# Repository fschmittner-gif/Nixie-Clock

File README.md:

# Nixie Clock

The goal of this project is to build your own Nixie Clock and get a result like this: 

## Resources
### Controlling the Tubes

The project is based on the idea of controlling the Nixie tubes with old russian driver parts utilizing an arduino nano based on this [article](https://www.instructables.com/Controlling-Nixie-Tube-With-Arduino-Using-K155ID1-/) 

### Real Time Clock (RTC)

In order to keep the time during a power outage or when moving the clock a RTC added to the project. For this purpose the DS3231 was used due to its low cost, easy I2C comunnication and available Arduino libraries.

## Designing the PCB

For the PCB Design a Schematic and Layout were designed in Fusion 360 and available for download and use. Before ordering your own PCBs, the DC Jack placement should be adapted as in the current design it sits inverted on the TOP Side. For my build, I fixed it by manipulating the installed DC Jack before soldering it onto the PCB.  

Rendering of PCB V1:

## BOM

| Reference Designators | Quantity | Description | Package | Value |
|---|---|---|---|---|
| ARDUINO_NANO | 1 | Arduino Nano V3.0 | ARDUINO_NANO |  |
| C1, C2, C3, C4, C5 | 5 | CAPACITOR, European symbol | C0603 | 100n |
| C6, C7 | 2 | CAPACITOR, European symbol | C0603 | 10u |
| D1 | 1 | DCDC Converter | NIXIE_DCDC | DCDC_NIXIE |
| DC_JACK | 1 | 2.1mm x 5.5mm THM DC jack with internal switch. Digikey part #PJ-102A, 4UCON part #05537 | PJ-102A | 2.1MMJACKTHM |
| DCDC_IN, DCDC_OUT | 2 | PIN HEADER | 1X02 |  |
| L1 | 1 | Linear Regulator 5V | TO220 | L7805_5V |
| NX1, NX2, NX3, NX4 | 4 | IN-14: medium numeric frontview nixie tube | IN-14 | IN-14 |
| R1, R2, R3, R4 | 4 | RESISTOR, European symbol | R1206 | 10k |
| RTC | 1 | RTC Module with Battery and EEPROM based on DS3231 and AT24C32 chips | RTC-DS3231-AT24C32 | RTC-DS3231-AT24C32 |
| U1, U2, U3, U4 | 4 | Nixie Drivers | DIL16 | K155ID1 |

## Software

The Software is split into 2 parts: "SetTime" and "Control".

First the "SetTime" code has to be flashed to the Arduino in order to set the RTC to the current time. Afterwards the "Coltrol" code shall be flashed to actually display the time on the Nixie Tubes. I recommend using the Arduino IDE for programming.

## Case

A ready to print 3D case for the designed PCB is available to download. 

## Lizenzierung

Dieses Projekt ist dual lizenziert:
- Die **Software und Firmware** steht unter der [Apache 2.0 Lizenz](LICENSE-SOFTWARE).
- Die **Hardware-Designs** (Schaltpläne, CAD-Daten, PCB-Layouts) stehen unter der [CERN-OHL-P v2 Lizenz](LICENSE-HARDWARE).

Beide Lizenzen schließen jegliche Haftung oder Gewährleistung aus. Die Nutzung erfolgt auf eigene Gefahr.

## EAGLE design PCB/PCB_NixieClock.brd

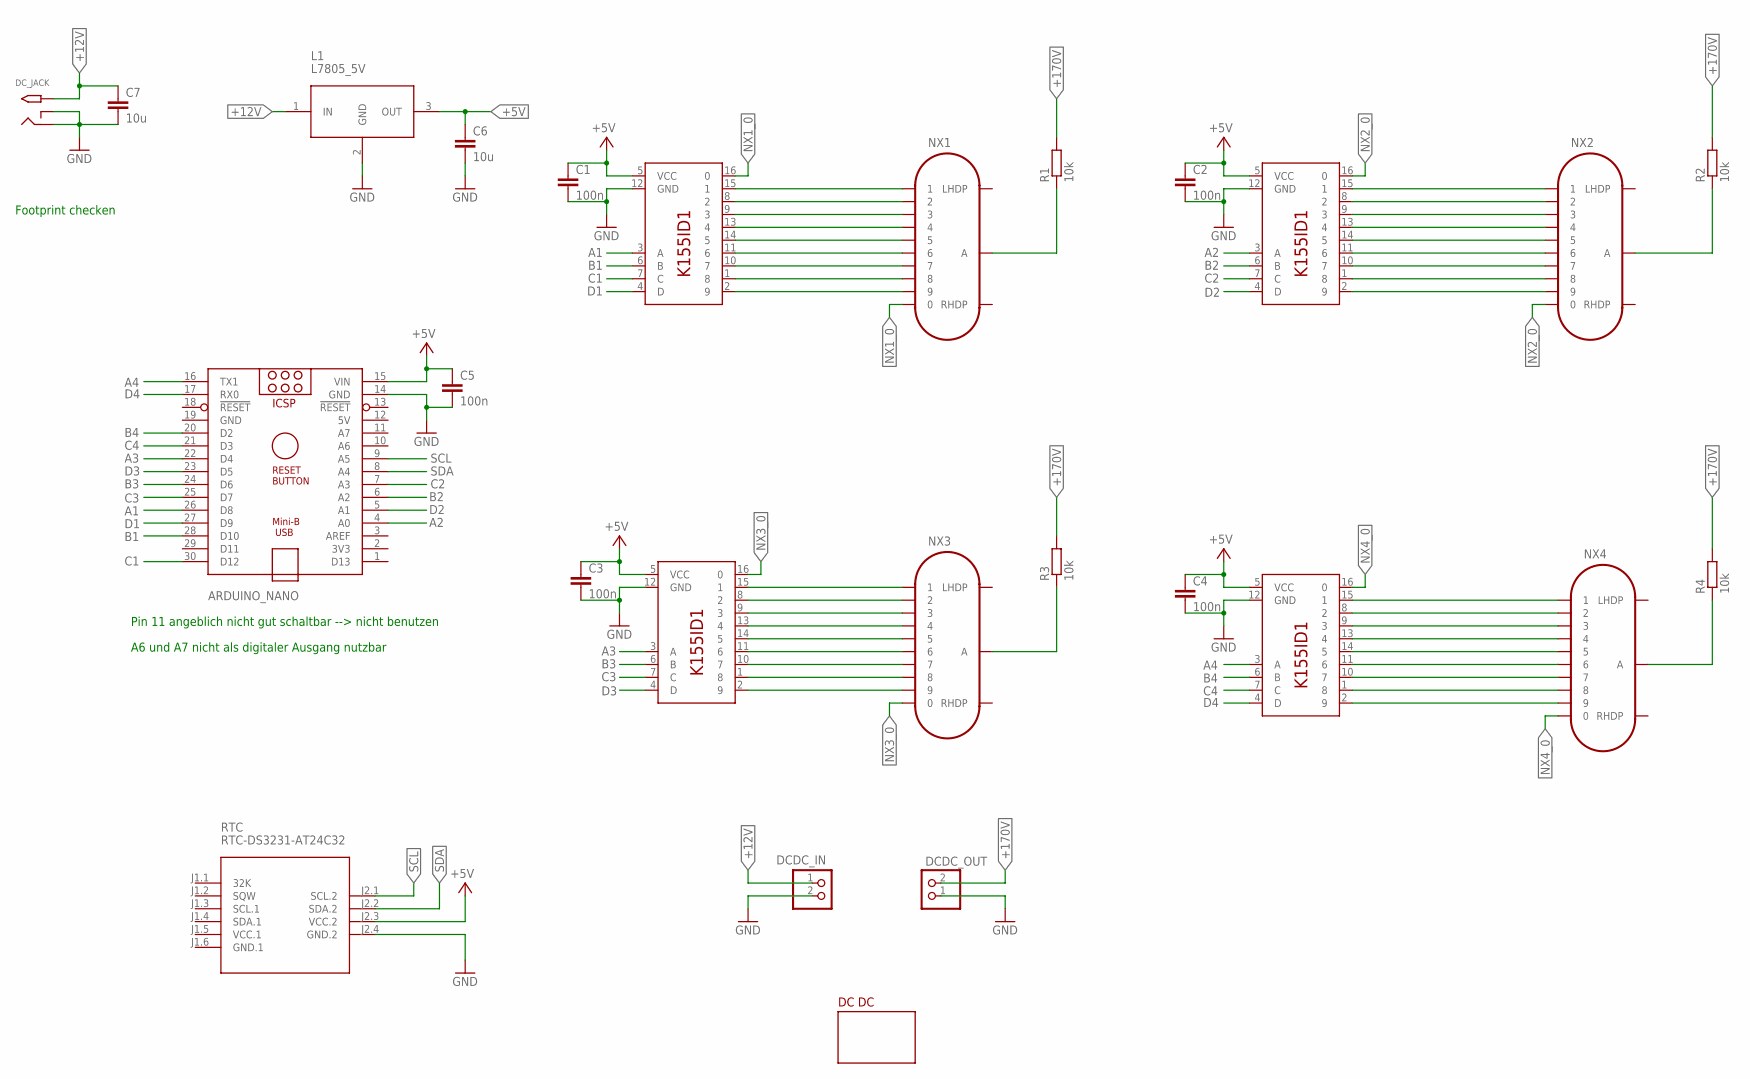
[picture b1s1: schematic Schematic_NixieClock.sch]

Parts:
ARDUINO_NANO: ARDUINO_NANO
C1, C2, C3, C4, C5: 100n; C0603
C6, C7: 10u; C0603
D1: DCDC_NIXIE; NIXIE_DCDC
DCDC_IN: PINHD-1X2; 1X02
DCDC_OUT: PINHD-1X2; 1X02
DC_JACK: 2.1MMJACKTHM; PJ-102A
L1: L7805_5V; TO220
NX1, NX2, NX3, NX4: IN-14
R1, R2, R3, R4: 10k; R1206
RTC: RTC-DS3231-AT24C32
U1, U2, U3, U4: K155ID1; DIL16

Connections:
5V: ARDUINO_NANO.12 (5V)
+5V: ARDUINO_NANO.15 (VIN), C1.1, C2.1, C3.1, C4.1, C5.1, C6.1, L1.3 (OUT), RTC.J2.3 (VCC.2), U1.5 (VCC), U2.5 (VCC), U3.5 (VCC), U4.5 (VCC)
+12V: C7.1, DCDC_IN.1, DC_JACK.TIP, L1.1 (IN)
+170V: DCDC_OUT.2, R1.2, R2.2, R3.2, R4.2
A1: ARDUINO_NANO.26 (D8), U1.3 (A)
A2: ARDUINO_NANO.4 (A0), U3.3 (A)
A3: ARDUINO_NANO.22 (D4), U2.3 (A)
A4: ARDUINO_NANO.16 (TX1), U4.3 (A)
B1: ARDUINO_NANO.28 (D10), U1.6 (B)
B2: ARDUINO_NANO.6 (A2), U3.6 (B)
B3: ARDUINO_NANO.24 (D6), U2.6 (B)
B4: ARDUINO_NANO.20 (D2), U4.6 (B)
C1: ARDUINO_NANO.30 (D12), U1.7 (C)
C2: ARDUINO_NANO.7 (A3), U3.7 (C)
C3: ARDUINO_NANO.25 (D7), U2.7 (C)
C4: ARDUINO_NANO.21 (D3), U4.7 (C)
D1: ARDUINO_NANO.27 (D9), U1.4 (D)
D2: ARDUINO_NANO.5 (A1), U3.4 (D)
D3: ARDUINO_NANO.23 (D5), U2.4 (D)
D4: ARDUINO_NANO.17 (RX0), U4.4 (D)
GND: ARDUINO_NANO.14 (GND), ARDUINO_NANO.19 (GND), C1.2, C2.2, C3.2, C4.2, C5.2, C6.2, C7.2, DCDC_IN.2, DCDC_OUT.1, DC_JACK.RING, DC_JACK.RING_SW, L1.2 (GND), RTC.J2.4 (GND.2), U1.12 (GND), U2.12 (GND), U3.12 (GND), U4.12 (GND)
GND.1: RTC.J1.6 (GND.1)
unnamed: NX1.1, U1.15 (1)
unnamed: NX1.2, U1.8 (2)
unnamed: NX1.3, U1.9 (3)
unnamed: NX1.4, U1.13 (4)
unnamed: NX1.5, U1.14 (5)
unnamed: NX1.6, U1.11 (6)
unnamed: NX1.7, U1.10 (7)
unnamed: NX1.8, U1.1 (8)
unnamed: NX1.9, U1.2 (9)
unnamed: NX3.1, U2.15 (1)
unnamed: NX3.2, U2.8 (2)
unnamed: NX3.3, U2.9 (3)
unnamed: NX3.4, U2.13 (4)
unnamed: NX3.5, U2.14 (5)
unnamed: NX3.6, U2.11 (6)
unnamed: NX3.7, U2.10 (7)
unnamed: NX3.8, U2.1 (8)
unnamed: NX3.9, U2.2 (9)
unnamed: NX2.1, U3.15 (1)
unnamed: NX2.2, U3.8 (2)
unnamed: NX2.3, U3.9 (3)
unnamed: NX2.4, U3.13 (4)
unnamed: NX2.5, U3.14 (5)
unnamed: NX2.6, U3.11 (6)
unnamed: NX2.7, U3.10 (7)
unnamed: NX2.8, U3.1 (8)
unnamed: NX2.9, U3.2 (9)
unnamed: NX4.1, U4.15 (1)
unnamed: NX4.2, U4.8 (2)
unnamed: NX4.3, U4.9 (3)
unnamed: NX4.4, U4.13 (4)
unnamed: NX4.5, U4.14 (5)
unnamed: NX4.6, U4.11 (6)
unnamed: NX4.7, U4.10 (7)
unnamed: NX4.8, U4.1 (8)
unnamed: NX4.9, U4.2 (9)
unnamed: NX3.A, R3.1
unnamed: NX1.A, R1.1
unnamed: NX2.A, R2.1
unnamed: NX4.A, R4.1
NX1_0: NX1.0, U1.16 (0)
NX2_0: NX2.0, U3.16 (0)
NX3_0: NX3.0, U2.16 (0)
NX4_0: NX4.0, U4.16 (0)
SCL: ARDUINO_NANO.9 (A5), RTC.J2.1 (SCL.2)
SDA: ARDUINO_NANO.8 (A4), RTC.J2.2 (SDA.2)
VCC.1: RTC.J1.5 (VCC.1)

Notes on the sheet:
Pin 11 angeblich nicht gut schaltbar --> nicht benutzen
A6 und A7 nicht als digitaler Ausgang nutzbar
Footprint checken

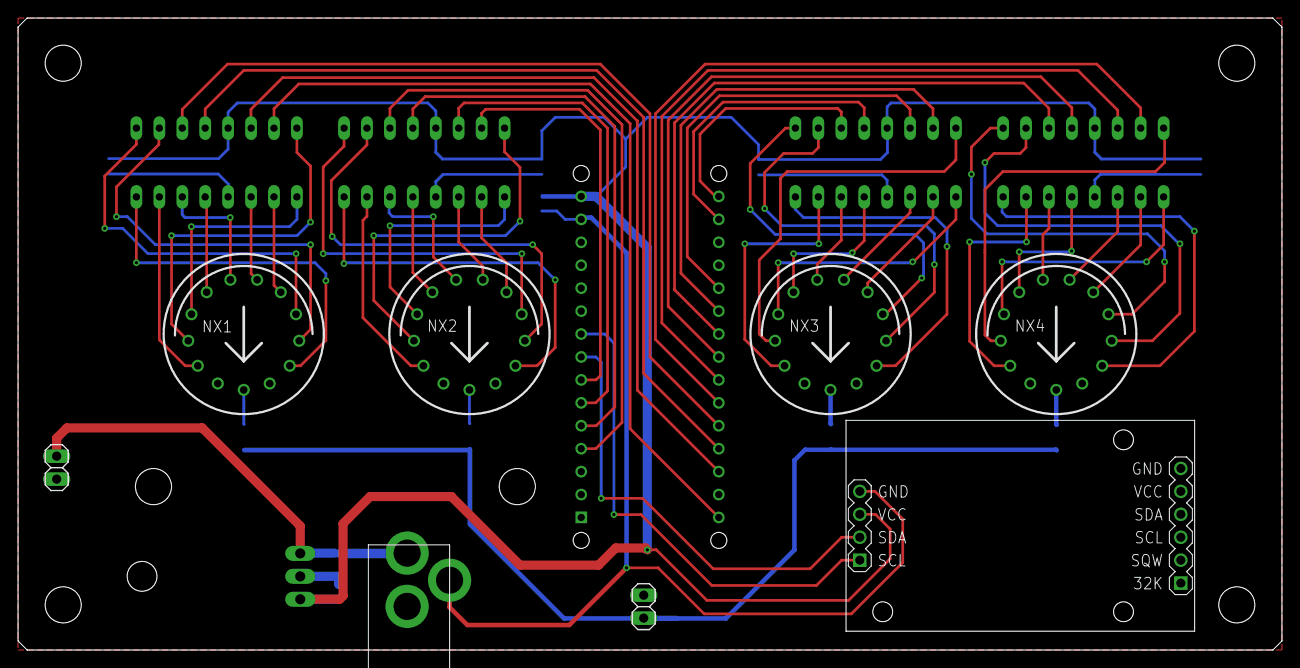
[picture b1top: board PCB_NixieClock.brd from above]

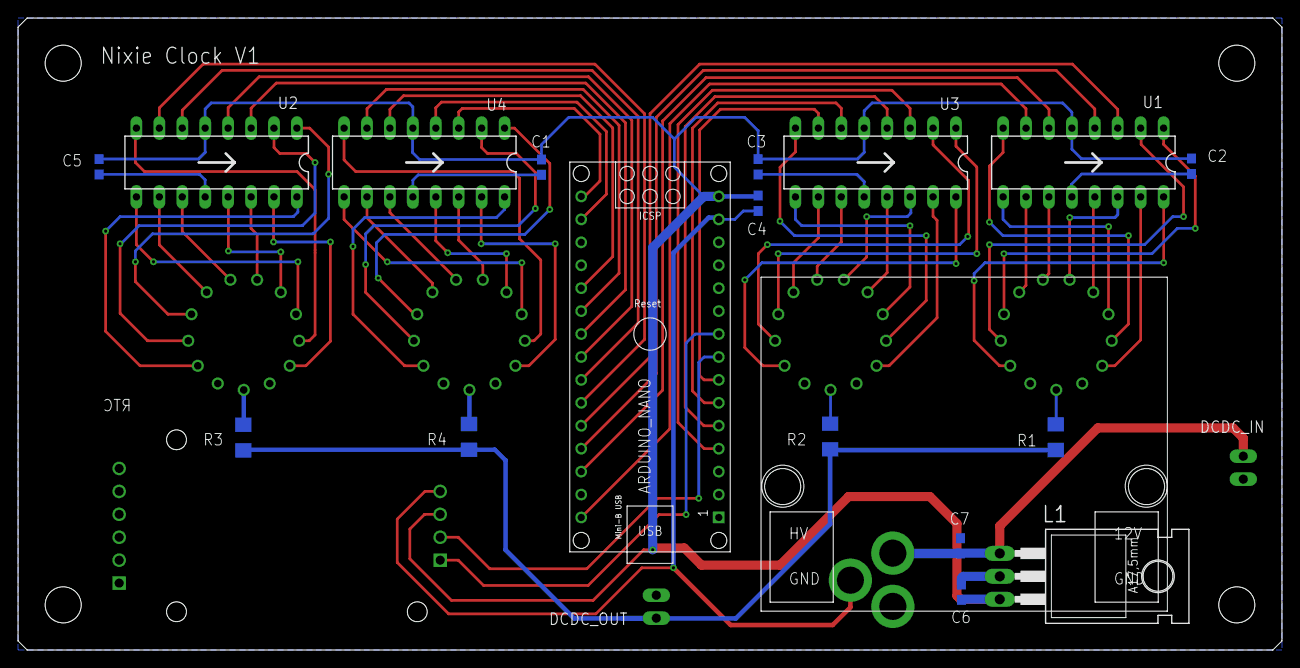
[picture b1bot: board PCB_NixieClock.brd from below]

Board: 2 copper layers, 140.0 x 70.0 mm, 26 parts (18 on the bottom side), 66 nets.

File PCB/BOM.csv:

Reference Designators	Quantity	Description	Package	Value
	1	Board	Board	
ARDUINO_NANO	1	Arduino Nano V3.0	ARDUINO_NANO	
C1, C2, C3, C4, C5	5	CAPACITOR, European symbol	C0603	100n
C6, C7	2	CAPACITOR, European symbol	C0603	10u
D1	1	DCDC Converter	NIXIE_DCDC	DCDC_NIXIE
DC_JACK	1	2.1mm x 5.5mm THM DC jack with internal switch. Digikey part #PJ-102A, 4UCON part #05537	PJ-102A	2.1MMJACKTHM
DCDC_IN, DCDC_OUT	2	PIN HEADER	1X02	
L1	1	Linear Regulator 5V	TO220	L7805_5V
NX1, NX2, NX3, NX4	4	IN-14: medium numeric frontview nixie tube	IN-14	IN-14
R1, R2, R3, R4	4	RESISTOR, European symbol	R1206	10k
RTC	1	RTC Module with Battery and EEPROM based on DS3231 and AT24C32 chips	RTC-DS3231-AT24C32	RTC-DS3231-AT24C32
U1, U2, U3, U4	4	Nixie Driverts	DIL16	K155ID1

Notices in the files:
parts and their libraries:
diy-modules: Released under the Creative Commons Attribution 4.0 International License: http://creativecommons.org/licenses/by/4.0
